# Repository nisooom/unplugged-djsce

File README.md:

# Hardware Hackathon - IoT for Urban Management

This repository contains all resources for our hardware hackathon project that implements an IoT system for urban management.

[Documentation](pcb/src/ERGA%20LABS.docx)
[PPT](pcb/src/erga%20labs.pptx)

[Supporting Dashboard UI](https://djiot.vercel.app/)

## Project Structure

### PCB Design

- **Source Files**: [pcb/src/](pcb/src/)
  - [KiCad Schematic](pcb/src/testing.kicad_sch)
  - [KiCad PCB Layout](pcb/src/testing.kicad_pcb)
  - [Bill of Materials](pcb/src/bill-of-materials.csv)
  - [Gerber Files](pcb/src/gerber-files.zip) (manufacturing files)

### PCB Output & Documentation

- **Renders and Verification**: [pcb/output/](pcb/output/)
  - [Complete PCB Layout](pcb/output/complete_pcb_layout.jpeg)
  - [Schematic Diagram](pcb/output/schematic.jpeg)
  - [Top Copper Layer](pcb/output/top_copper.jpeg)
  - [Bottom Copper Layer](pcb/output/bottom_copper.jpeg)
  - [3D Representation](pcb/output/3d_representation.jpeg)
  - [Design Rule Check Results](pcb/output/design_rule_cheker.jpeg)
  - [Electrical Rule Check Results](pcb/output/electrical_rule_checker.jpeg)

### 3D Models

- **Enclosure Design**: [pcb/3D_CAD_Model/](pcb/3D_CAD_Model/)
  - [3D Model Preview](pcb/3D_CAD_Model/3d%20model.PNG)
  - [OBJ File](pcb/3D_CAD_Model/pcb%20bOX%20v1.obj)
  - [Material File](pcb/3D_CAD_Model/pcb%20bOX%20v1.mtl)

### User Interface

- **Dashboard Design**: [ui/dashboard.jpeg](ui/dashboard.jpeg)

### Hardware Requirements

- List of components (refer to [Bill of Materials](pcb/src/bill-of-materials.csv))

## Team Members

- Nishumbh Shah
- Dev Tangadi
- Hamza Murghay
- Tejas Bhovad
- Satish Singh
- Pranavi Shukla

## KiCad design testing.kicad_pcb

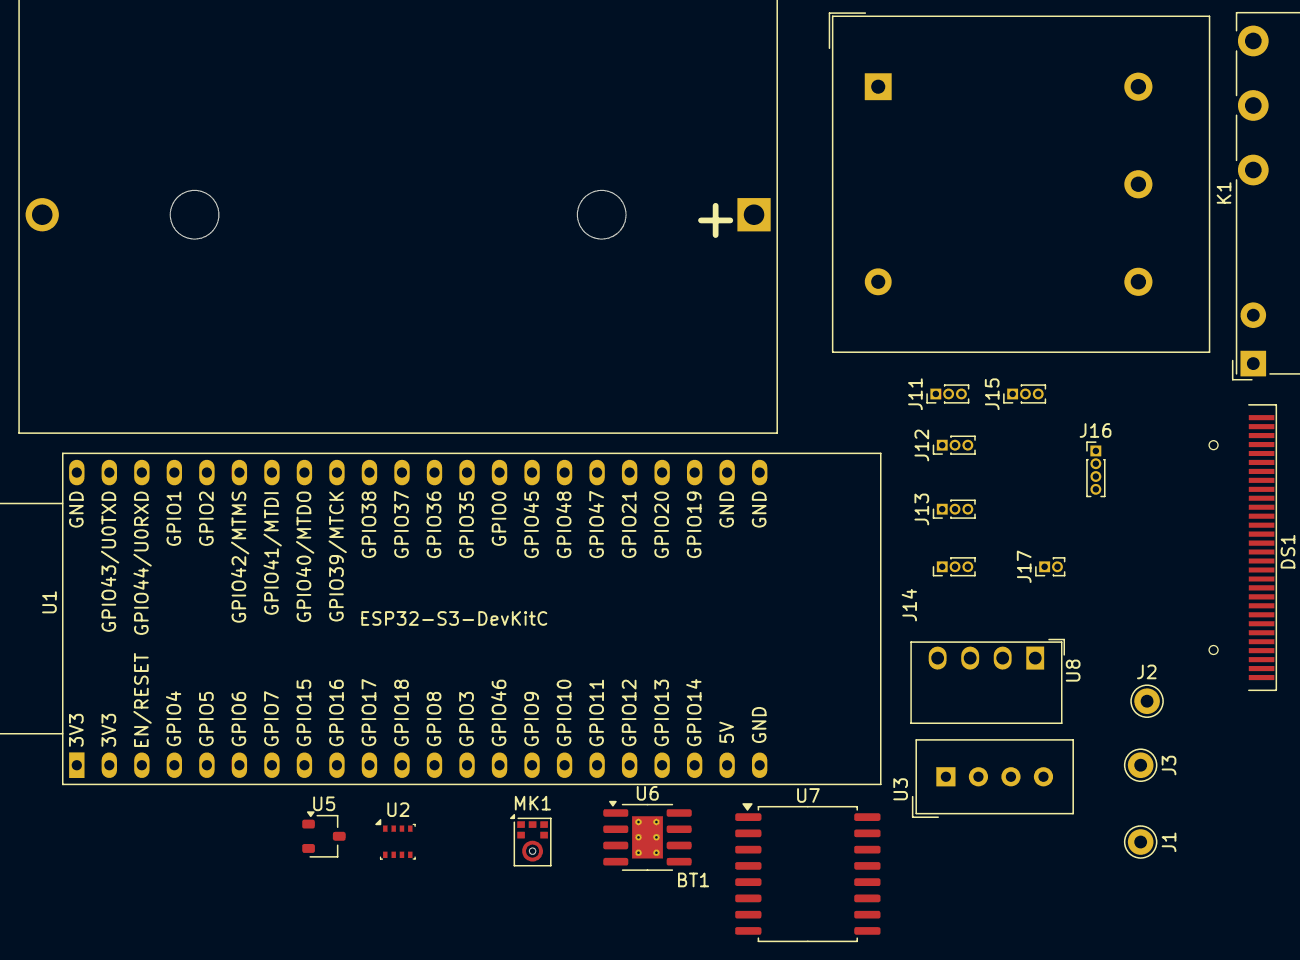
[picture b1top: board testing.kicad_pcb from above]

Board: 2 copper layers, 22 parts (0 on the bottom side), 34 nets, no tracks yet.

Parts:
BT1: Battery_Cell; BatteryHolder_Bulgin_BX0036_1xC
DS1: OLED-128O064D
J1: Conn_01x10_Pin 5V; Pin_D1.0mm_L10.0mm
J2: Conn_01x10_Pin 3.3V; Pin_D1.0mm_L10.0mm
J3: Conn_01x10_Pin GND; Pin_D1.0mm_L10.0mm
J11: Conn_01x03_Pin Water Flow; PinHeader_1x03_P1.00mm_Vertical
J12: 01x03 Flame; PinHeader_1x03_P1.00mm_Vertical
J13: Conn_01x03_Pin; PinHeader_1x03_P1.00mm_Vertical
J14: Conn_01x03_Pin Sound; PinHeader_1x03_P1.00mm_Vertical
J15: Conn_01x04_Pin Rain; PinHeader_1x03_P1.00mm_Vertical
J16: Conn_01x04_Pin Soil Humidity; PinHeader_1x04_P1.00mm_Vertical
J17: Conn_01x02_Pin; PinHeader_1x02_P1.00mm_Vertical
K1: Fujitsu_FTR-LYCA005x; Relay_SPDT_Fujitsu_FTR-LYCA005x_FormC_Vertical
MK1: ICS-43434; InvenSense_ICS-43434-6_3.5x2.65mm
U1: ESP32-S3-DevKitC
U2: BME280 - Pressure Humidity Sensor; Bosch_LGA-8_2.5x2.5mm_P0.65mm_ClockwisePinNumbering
U3: DHT11 Temp Sensor; Aosong_DHT11_5.5x12.0_P2.54mm
U5: A1101ELHL Hall Effect; SOT-23W
U6: TP4056-42-ESOP8 - Battery Recharger; SOIC-8-1EP_3.9x4.9mm_P1.27mm_EP2.41x3.3mm_ThermalVias
U7: DS3231M - RTC; SOIC-16W_7.5x10.3mm_P1.27mm
U8: CRE1S0305S3C; Converter_DCDC_Murata_CRE1xxxxxx3C_THT
VoltageSensorU6: LV25-P; LEM_LV25-P

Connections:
unnamed: BT1.1 (+), J2.1, J11.3, J12.3, J16.4, MK1.5 (VDD), U1.1 (3V3), U1.2 (3V3), U1.21 (5V), U2.2 (CSB), U2.6 (VDDIO), U2.8 (VDD), U3.1 (VDD), U5.1 (VCC), U6.5 (BAT), U6.8 (CE), U7.2 (VCC), U7.3 (~INT/SQW), U7.4 (~RST), U8.2 (+VIN)
unnamed: BT1.2 (-), DS1.1 (GND), DS1.2 (C2N), DS1.3 (C2P), DS1.4 (C1P), DS1.5 (C1N), DS1.8 (VSS), DS1.26 (IREF), DS1.27 (VCOMH), DS1.29 (VLSS), DS1.30 (GND), J3.1, J11.1, J12.1, J13.1, J14.1, J15.1, J16.1, MK1.3 (GND), U1.3 (CHIP_PU), U1.8 (GPIO15/ADC2_CH4/32K_P), U1.9 (GPIO16/ADC2_CH5/32K_N), U1.22 (GND), U1.23 (GND), U1.24 (GND), U1.25 (GPIO19/USB_D-), U1.26 (GPIO20/USB_D+), U1.38 (GPIO41/MTDI), U1.39 (GPIO42/MTMS), U1.42 (GPIO44/U0RXD), U1.43 (GPIO43/U0TXD), U1.44 (GND), U2.1 (GND), U2.5 (SDO), U2.7 (GND), U3.4 (GND), U5.3 (GND), U6.1 (TEMP), U6.2 (PROG), U6.3 (GND), U7.1 (32KHZ), U7.5 (GND), U7.6 (GND), U7.7 (GND), U7.8 (GND), U7.9 (GND), U7.10 (GND), U7.11 (GND), U7.12 (GND), U7.13 (GND), U8.1 (-VIN), U8.3 (-VOUT), VoltageSensorU6.3 (HV-), VoltageSensorU6.6 (V-)
unnamed: DS1.6 (VBAT), DS1.9 (VDD), DS1.10 (BS0), DS1.11 (BS1), DS1.12 (BS2), DS1.13 (~CS), DS1.14 (~RES), DS1.15 (D/~C), DS1.16 (R/~W), DS1.17 (E/~RD), DS1.28 (VCC), J1.1, J13.3, J14.3, K1.11, U8.4 (+VOUT), VoltageSensorU6.1 (HV+)
unnamed: DS1.18 (D0), U1.31 (GPIO0)
unnamed: DS1.19 (D1), U1.41 (GPIO1/ADC1_CH0)
unnamed: DS1.20 (D2), U1.40 (GPIO2/ADC1_CH1)
unnamed: DS1.21 (D3), U1.13 (GPIO3/ADC1_CH2)
unnamed: DS1.22 (D4), U1.4 (GPIO4/ADC1_CH3)
unnamed: DS1.23 (D5), U1.5 (GPIO5/ADC1_CH4)
unnamed: DS1.24 (D6), U1.6 (GPIO6/ADC1_CH5)
unnamed: DS1.25 (D7), U1.7 (GPIO7/ADC1_CH6)
unnamed: J11.2, U1.10 (GPIO17/ADC2_CH6)
unnamed: J12.2, U1.20 (GPIO14/ADC2_CH3), U7.14 (VBAT)
unnamed: J13.2, U1.19 (GPIO13/ADC2_CH2)
unnamed: J14.2, U1.18 (GPIO12/ADC2_CH1)
unnamed: J15.2, U1.16 (GPIO10/ADC1_CH9)
unnamed: J15.3, U1.17 (GPIO11/ADC2_CH0)
unnamed: J16.2, U1.37 (GPIO40/MTDO)
unnamed: J16.3, U1.36 (GPIO39/MTCK)
unnamed: J17.1, K1.12
unnamed: J17.2, K1.14
unnamed: MK1.4 (SCK), U1.28 (GPIO47)
unnamed: MK1.6 (SD), U1.29 (GPIO48)
unnamed: MK1.1 (WS), U1.14 (GPIO46)
unnamed: K1.A1, U1.12 (GPIO8/ADC1_CH7)
unnamed: K1.A2, U1.15 (GPIO9/ADC1_CH8)
unnamed: U1.11 (GPIO18/ADC2_CH7), VoltageSensorU6.4 (M)
unnamed: U1.27 (GPIO21), U7.15 (SDA)
unnamed: U1.32 (GPIO35), U7.16 (SCL)
unnamed: U1.33 (GPIO36), U5.2 (VOUT)
unnamed: U1.34 (GPIO37), U2.3 (SDI)
unnamed: U1.35 (GPIO38), U2.4 (SCK)
unnamed: U1.30 (GPIO45), U3.2 (DATA)
unnamed: U6.6 (~STDBY), U6.7 (~CHRG)

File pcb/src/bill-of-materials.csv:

"Reference","Qty","Value","DNP","Exclude from BOM","Exclude from Board","Footprint","Datasheet"
"BT1","1","Battery_Cell","","","","Battery:BatteryHolder_Bulgin_BX0036_1xC","~"
"DS1","1","OLED-128O064D","","","","Display:OLED-128O064D","https://www.vishay.com/docs/37902/oled128o064dbpp3n00000.pdf"
"J1","1","Conn_01x10_Pin 5V","","","","Connector_Pin:Pin_D1.0mm_L10.0mm","~"
"J2","1","Conn_01x10_Pin 3.3V","","","","Connector_Pin:Pin_D1.0mm_L10.0mm","~"
"J3","1","Conn_01x10_Pin GND","","","","Connector_Pin:Pin_D1.0mm_L10.0mm","~"
"J4","1","Conn_01x01","","","","","~"
"J11","1","Conn_01x03_Pin Water Flow","","","","Connector_PinHeader_1.00mm:PinHeader_1x03_P1.00mm_Vertical","~"
"J12","1","01x03 Flame","","","","Connector_PinHeader_1.00mm:PinHeader_1x03_P1.00mm_Vertical","~"
"J13","1","Conn_01x03_Pin","","","","Connector_PinHeader_1.00mm:PinHeader_1x03_P1.00mm_Vertical","~"
"J14","1","Conn_01x03_Pin Sound","","","","Connector_PinHeader_1.00mm:PinHeader_1x03_P1.00mm_Vertical","~"
"J15","1","Conn_01x04_Pin Rain","","","","Connector_PinHeader_1.00mm:PinHeader_1x03_P1.00mm_Vertical","~"
"J16","1","Conn_01x04_Pin Soil Humidity","","","","Connector_PinHeader_1.00mm:PinHeader_1x04_P1.00mm_Vertical","~"
"J17","1","Conn_01x02_Pin","","","","Connector_PinHeader_1.00mm:PinHeader_1x02_P1.00mm_Vertical","~"
"K1","1","Fujitsu_FTR-LYCA005x","","","","Relay_THT:Relay_SPDT_Fujitsu_FTR-LYCA005x_FormC_Vertical","https://www.fujitsu.com/sg/imagesgig5/ftr-ly.pdf"
"MK1","1","ICS-43434","","","","Sensor_Audio:InvenSense_ICS-43434-6_3.5x2.65mm","https://www.invensense.com/wp-content/uploads/2016/02/DS-000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"
"SC1","1","Solar_Cells","","","","Connector_PinHeader_1.00mm:PinHeader_2x03_P1.00mm_Vertical","~"
"U1","1","ESP32-S3-DevKitC","","","","PCM_Espressif:ESP32-S3-DevKitC",""
"U2","1","BME280 - Pressure Humidity Sensor","","","","Package_LGA:Bosch_LGA-8_2.5x2.5mm_P0.65mm_ClockwisePinNumbering","https://www.bosch-sensortec.com/media/boschsensortec/downloa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"
"U3","1","DHT11 Temp Sensor","","","","Sensor:Aosong_DHT11_5.5x12.0_P2.54mm","http://akizukidenshi.com/download/ds/aosong/DHT11.pdf"
"U5","1","A1101ELHL Hall Effect","","","","Package_TO_SOT_SMD:SOT-23W","https://www.allegromicro.com/-/media/files/datasheets/a110x-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"
"U6","1","TP4056-42-ESOP8 - Battery Recharger","","","","Package_SO:SOIC-8-1EP_3.9x4.9mm_P1.27mm_EP2.41x3.3mm_ThermalVias","https://www.lcsc.com/datasheet/lcsc_datasheet_2410121619_TOP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"
"U7","1","DS3231M - RTC","","","","Package_SO:SOIC-16W_7.5x10.3mm_P1.27mm","http://datasheets.maximintegrated.com/en/ds/DS3231.pdf"
"U8","1","CRE1S0305S3C","","","","Converter_DCDC:Converter_DCDC_Murata_CRE1xxxxxx3C_THT","http://power.murata.com/datasheet?/data/power/ncl/kdc_cre1.pdf"
"VoltageSensorU6","1","LV25-P","","","","Sensor_Voltage:LEM_LV25-P","https://www.lem.com/sites/default/files/products_datasheets/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"

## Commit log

2025-03-08 init
2025-03-08 chore: organised
2025-03-08 add: 3D CAD Model
2025-03-08 feat: add gerber
2025-03-08 fix:erc
2025-03-08 add: .stl and .f3d model files
2025-03-08 feat: add readme
2025-03-08 feat: docs
2025-03-08 chore: refactor
2025-03-08 chore : add site
2025-03-09 test
2025-03-09 cleanup
